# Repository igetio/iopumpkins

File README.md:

# IO Pumpkins
* [Pumpkin Control Project Overview](#pumpkin-control-project-overview)
* [Raspberrypi Setup](#raspberrypi-setup)
  + [Installing RabbitMQ and MQTT](#installing-rabbitmq-and-mqtt)
    - [Basic Setup of RabbitMQ](#basic-setup-of-rabbitmq)
    - [Optional - Install RabbitMQ admin site](#optional---install-rabbitmq-admin-site)
  + [Setting up Node site:](#setting-up-node-site)
    - [Basic Setup of Node and sqlite3](#basic-setup-of-node-and-sqlite3)
    - [Running Node as Background Process:](#running-node-as-background-process)
* [Arduino Setup](#arduino-setup)
  + [Basic IDE setup](#basic-ide-setup)

## Pumpkin Control Project Overview
The purpose of this project is to create a raspberry pi controller for a haloween display. It uses node and mqtt running on the rasspberrypi. It uses esp8266 wifi cards to communicate with MQTT and the raspberrypi manages what actions to take for each module and places the messages into MQTT for the modules to process.

There are two parts to this project the rapsberrypi setup and configuration and the arduino module setup 

## Raspberrypi Setup

### Installing RabbitMQ and MQTT
#### Basic Setup of RabbitMQ
1. Install Rabbitmq
    1. Run `sudo apt-get install rabbitmq-server`
2. Install MQTT Plugin
    1. Run `rabbitmq-plugins enable rabbitmq_mqtt`
    2. Run `rabbitmqctl add_user mqtt-test mqtt-test`
    3. Run `rabbitmqctl set_permissions -p / mqtt-test ".*" ".*" ".*"`
    4. Run `rabbitmqctl set_user_tags mqtt-test management`
#### Optional - Install RabbitMQ admin site
1. Run `rabbitmq-plugins enable rabbitmq_management`
2. Create Admin account for login
    1. Run `rabbitmqctl add_user admin admin-password`
    2. Run `rabbitmqctl set_permissions -p / admin ".*" ".*" ".*"`
    3. Run `rabbitmqctl set_user_tags admin administrator`
3. Connect to Console via https://<SERVERNAME>:15672

### Setting up Node site
#### Basic Setup of Node and sqlite3
(The version on my pi is currently v8.x LTS)
1. Install node.js 
    1. Run `curl -sL https://deb.nodesource.com/setup_8.x | sudo -E bash -`
    2. Run `sudo apt install -y nodejs`
2. Install sqlite3
    1. Run `sudo apt-get install sqlite3`
3. Download this repo and extract it
4. Navigate to the nodejs/pumpkin folder and run `npm install`
    1. Optional update dependencies
        1. Run `sudo npm install -g npm-check-updates` 
        2. Run `ncu -u`
        3. Run `npm install`
5. Create the database with `sqlite3 pumpkinpi.db < pumpkinpi.sql`
6. Start the node server `npm start` 
#### Running Node as Background Process
1. Run `sudo npm install -g forever`
2. from the `nodejs/pumpkin` folder run `forever start -w ./bin/www`

## Arduino Setup
### Basic IDE setup

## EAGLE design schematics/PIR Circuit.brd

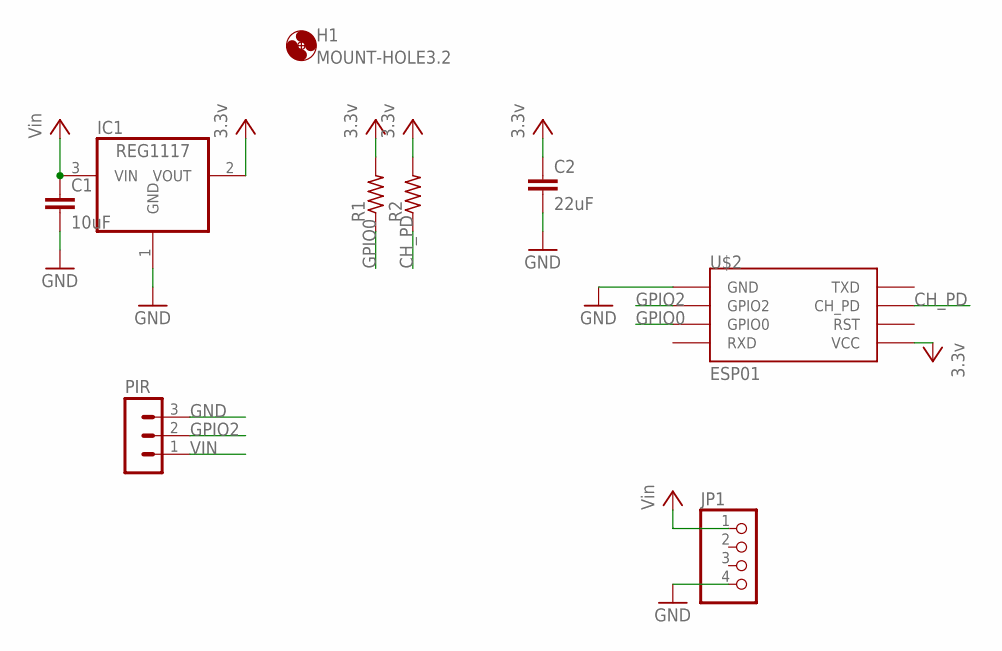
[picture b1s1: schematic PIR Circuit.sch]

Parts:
C1: 10uF; C0805
C2: 22uF; C0805
H1: MOUNT-HOLE3.2; 3,2
IC1: REG1117; SOT223
JP1: PINHD-1X4/90; 1X04/90
PIR: MA03-1
R1, R2: R-US_M1206; M1206
U$2: ESP01

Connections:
3.3V: C2.1, IC1.2 (VOUT), R1.2, R2.2, U$2.VCC
CH_PD: R2.1, U$2.CH_PD
GND: C1.2, C2.2, IC1.1 (GND), JP1.4, PIR.3, U$2.GND
GPIO0: R1.1, U$2.GPIO0
GPIO2: PIR.2, U$2.GPIO2
VIN: C1.1, IC1.3 (VIN), JP1.1, PIR.1

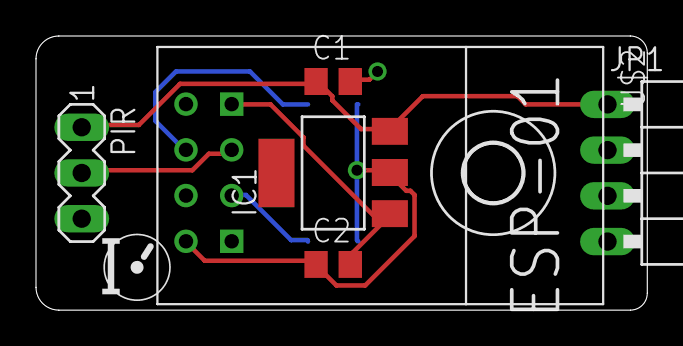
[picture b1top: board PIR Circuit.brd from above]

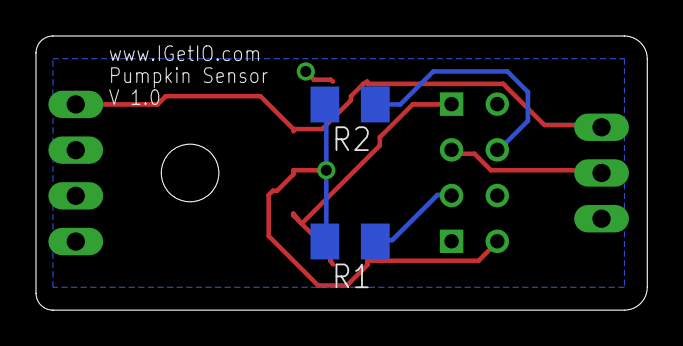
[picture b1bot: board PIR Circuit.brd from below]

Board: 2 copper layers, 34.0 x 15.2 mm, 10 parts (2 on the bottom side), 6 nets.

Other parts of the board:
U$1: IGETIO-0.25

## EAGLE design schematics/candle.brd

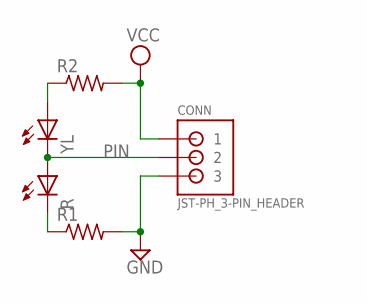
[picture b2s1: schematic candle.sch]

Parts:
CONN: JST-PH_3-PIN_HEADER; JST_B3B-PH_HEADER
R: LED3MM
R1, R2: R-US_M1206; M1206
YL: LED3MM

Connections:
GND: CONN.P3 (3), R1.2
unnamed: R2.1, YL.A
unnamed: R.K (C), R1.1
PIN: CONN.P2 (2), R.A, YL.K (C)
VCC: CONN.P1 (1), R2.2

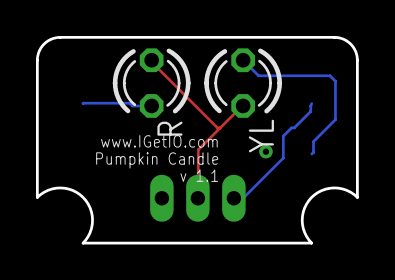
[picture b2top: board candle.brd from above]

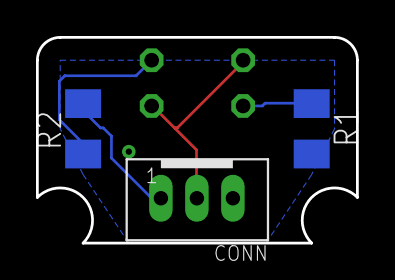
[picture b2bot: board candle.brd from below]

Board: 2 copper layers, 17.8 x 11.4 mm, 5 parts (3 on the bottom side), 5 nets.

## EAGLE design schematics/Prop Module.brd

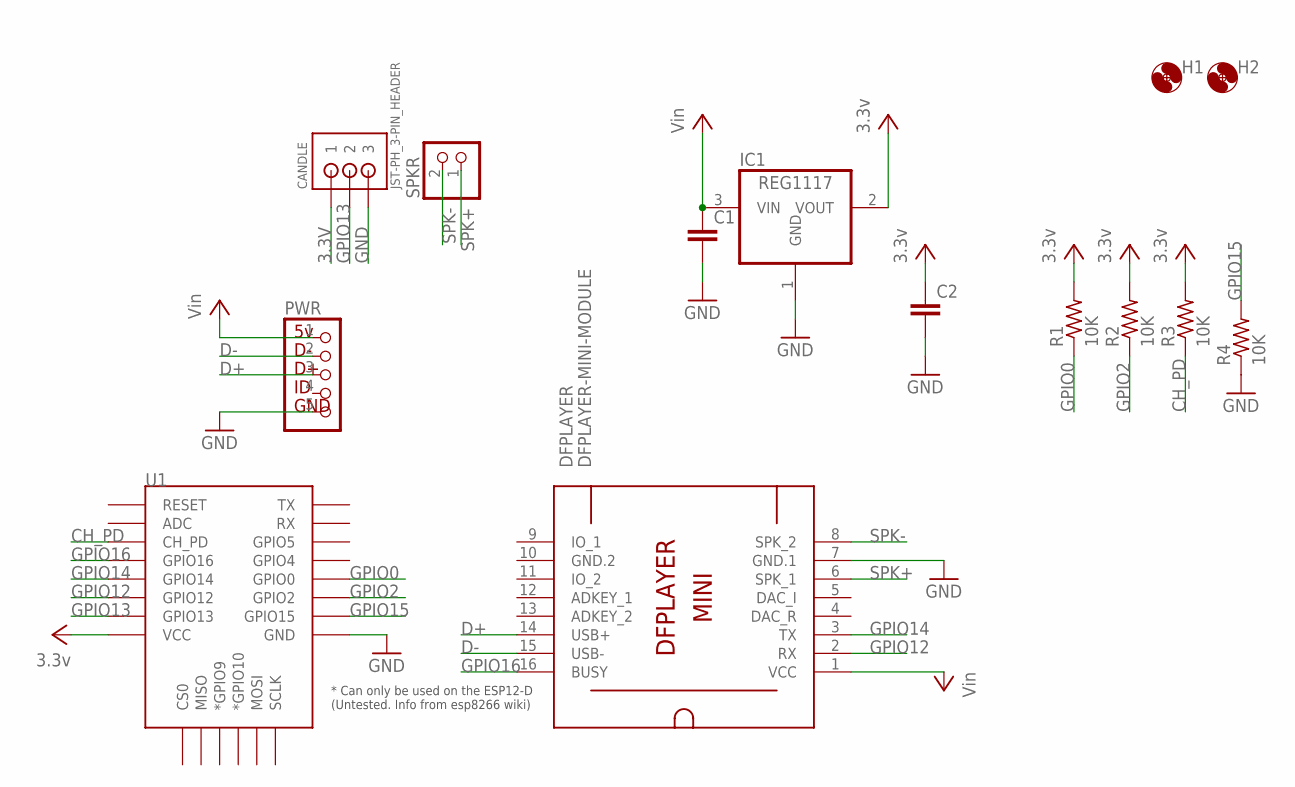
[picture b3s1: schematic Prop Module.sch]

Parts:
C1, C2: C; C0805
CANDLE: JST-PH_3-PIN_HEADER; JST_B3B-PH_HEADER
DFPLAYER: DFPLAYER-MINI-MODULE
H1, H2: MOUNT-HOLE3.2; 3,2
IC1: REG1117; SOT223
PWR: USB_BRK-1X5; 1X05
R1, R2, R3, R4: 10K; M1206
SPKR: JST_2PIN-THM; JST-PH-2-THM
U1: ESP12ESMD; ESP12E-SMD

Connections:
3.3V: C2.1, CANDLE.P1 (1), IC1.2 (VOUT), R1.2, R2.2, R3.2, U1.VCC
CH_PD: R3.1, U1.CH_PD
D+: DFPLAYER.14 (USB+), PWR.3
D-: DFPLAYER.15 (USB-), PWR.2
GND: C1.2, C2.2, CANDLE.P3 (3), DFPLAYER.7 (GND.1), IC1.1 (GND), PWR.5, R4.1, U1.GND
GND.2: DFPLAYER.10 (GND.2)
GPIO0: R1.1, U1.GPIO0
GPIO2: R2.1, U1.GPIO2
GPIO12: DFPLAYER.2 (RX), U1.GPIO12
GPIO13: CANDLE.P2 (2), U1.GPIO13
GPIO14: DFPLAYER.3 (TX), U1.GPIO14
GPIO15: R4.2, U1.GPIO15
GPIO16: DFPLAYER.16 (BUSY), U1.GPIO16
SPK+: DFPLAYER.6 (SPK_1), SPKR.1 (2)
SPK-: DFPLAYER.8 (SPK_2), SPKR.2 (1)
VIN: C1.1, DFPLAYER.1 (VCC), IC1.3 (VIN), PWR.1

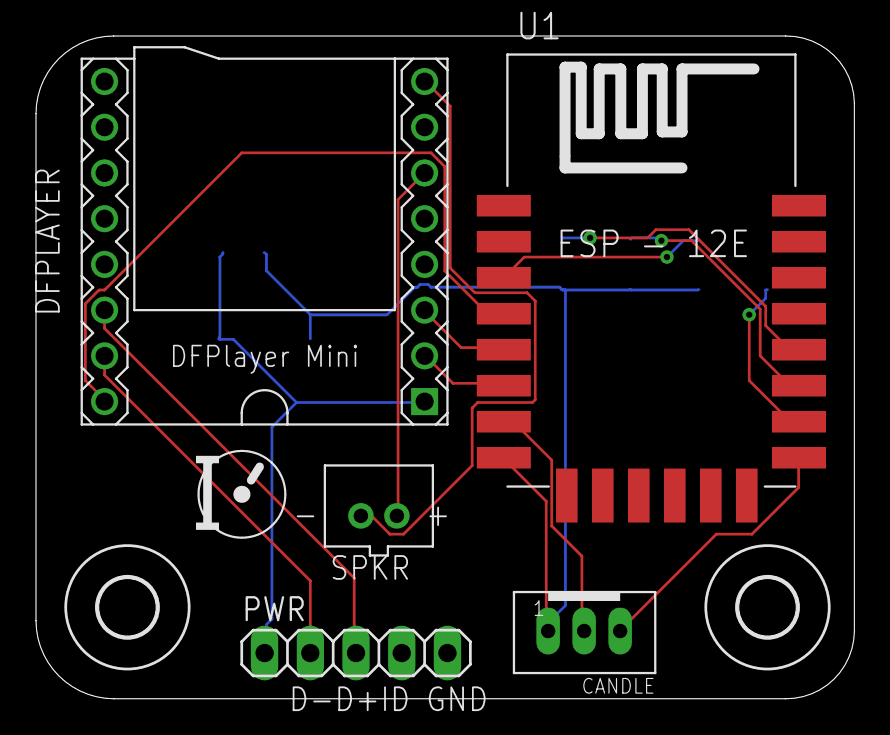
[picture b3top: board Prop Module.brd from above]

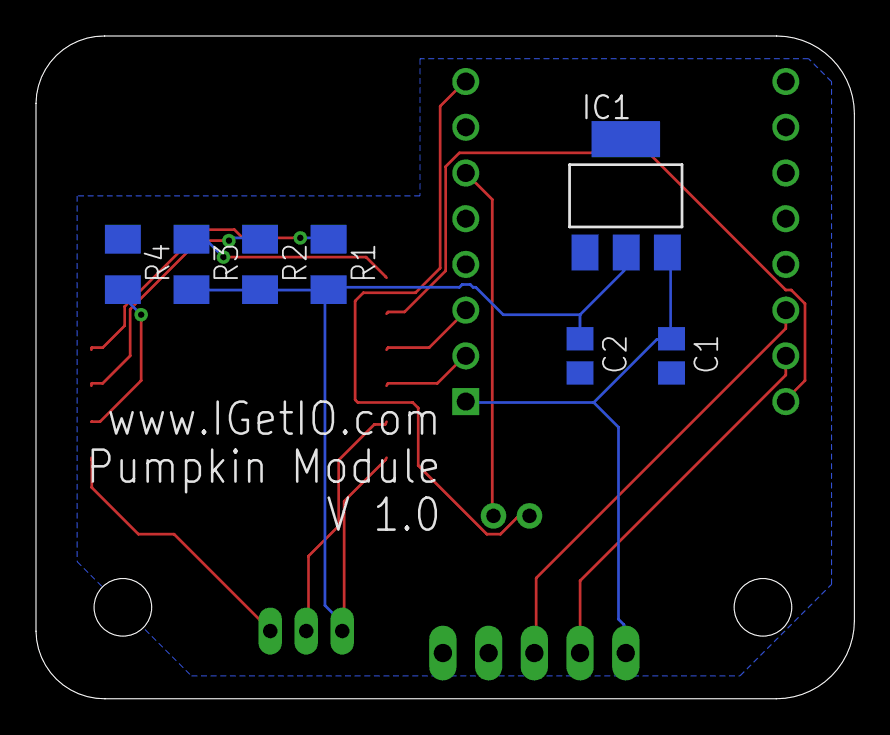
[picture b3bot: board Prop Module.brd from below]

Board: 2 copper layers, 45.5 x 36.8 mm, 15 parts (7 on the bottom side), 15 nets.

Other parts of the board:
U$1: IGETIO-0.33

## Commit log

2017-08-17 Initial Commit
    initial commit for iopumpkins
2017-09-17 Primary Update
    Adding all files to the project for current setup of scripts
2017-09-17 adding SQL script
    adding SQL setup script
2018-09-02 updating debug version
2018-09-02 Updating versions of dependencies
2018-09-02 Updating README
2018-09-02 Updating README again
2018-09-02 adding base folders for other elements
2018-09-02 Updating STLs
2018-09-02 Adding Schematics
2018-09-03 Adding MP3 fiels for talking modules

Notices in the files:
parts and their libraries:
diy-modules: Released under the Creative Commons Attribution 4.0 International License: http://creativecommons.org/licenses/by/4.0
